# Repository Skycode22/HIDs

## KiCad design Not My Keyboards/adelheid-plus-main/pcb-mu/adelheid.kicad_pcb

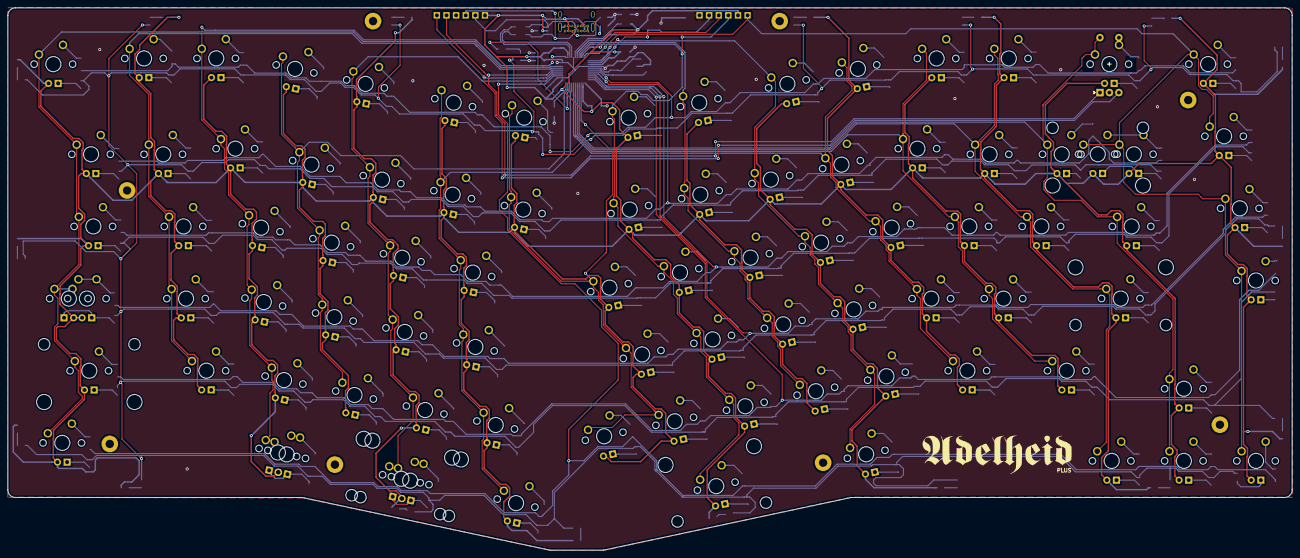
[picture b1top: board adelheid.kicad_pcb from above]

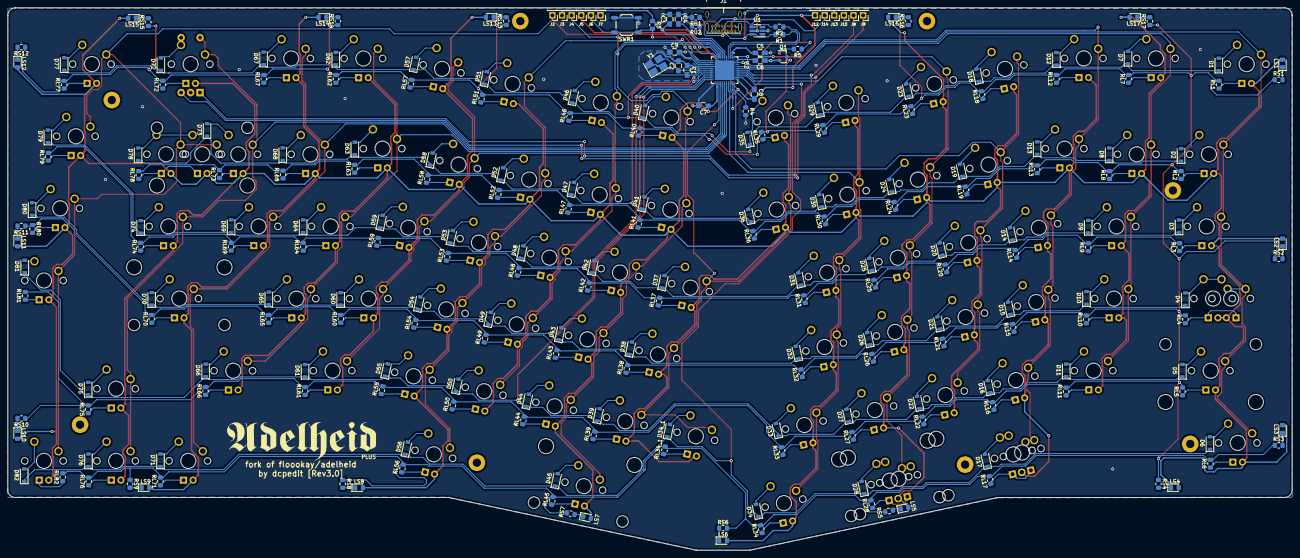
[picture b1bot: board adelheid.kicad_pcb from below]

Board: 2 copper layers, 339.1 x 143.2 mm, 332 parts (235 on the bottom side), 223 nets.

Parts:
 G2: LOGO; adelheid-logo
C1, C2: 22pF; C_0805_HandSoldering
C3: 10uF; C_0805_HandSoldering
C4: 1uF (±10%); C_0805_HandSoldering
C5: 1uF; C_0805_HandSoldering
C6, C7, C8, C9: 0.1uF; C_0805_HandSoldering
D1, D2, D3, D4, D5, D6, D7, D8, D9, D10, D11, D12, D13, D14, D15, D16, D17, D18, D19, D20, D21, D22, D23, D24, D25, D26, D27, D28, D29, D30, D31, D32, D33, D34, D34_1, D35, D36, D37, D38, D39, D40, D41, D42, D43, D44, D45, D46, D47, D48, D49, D50, D51, D52, D53, D54, D55, D56, D57, D58, D59, D60, D61, D62, D63, D64, D65, D66, D67, D68, D69, D70, D71, D72, D73, D74, D75, D76, D77, D78, D79, D80, D81, D82: D; D_SOD-123
G1: LOGO; adelheid-logo
H1, H2, H3, H4, H5, H6, H7, H8: MountingHole; MountingHole_2.2mm_M2_Pad
J1: USB_C_Receptacle_USB2.0; USB_C_GCT_USB4085
J2: MISO; Pin_Header_Straight_1x01_Pitch2.54mm
J3, J12: VCC; Pin_Header_Straight_1x01_Pitch2.54mm
J4: SCK; Pin_Header_Straight_1x01_Pitch2.54mm
J5: MOSI; Pin_Header_Straight_1x01_Pitch2.54mm
J6: RES; Pin_Header_Straight_1x01_Pitch2.54mm
J7, J15: GND; Pin_Header_Straight_1x01_Pitch2.54mm
J8: PF4; Pin_Header_Straight_1x01_Pitch2.54mm
J9: PF5; Pin_Header_Straight_1x01_Pitch2.54mm
J13: D+; Pin_Header_Straight_1x01_Pitch2.54mm
J14: D-; Pin_Header_Straight_1x01_Pitch2.54mm
LS1, LS2, LS3, LS4, LS5, LS6, LS7, LS8, LS9, LS10, LS11, LS12, LS13, LS14, LS15, LS16, LS17: LED; LED_0805_2012Metric_Pad1.15x1.40mm_HandSolder
MX1, MX2, MX7, MX8, MX9, MX10, MX11, MX12, MX13, MX14, MX15, MX16, MX18, MX19, MX20, MX21, MX22, MX23, MX24, MX25, MX26, MX27, MX29, MX30, MX31, MX32, MX33, MX34, MX34_1, MX35, MX36, MX37, MX38, MX39, MX40, MX41, MX42, MX43, MX44, MX46, MX47, MX48, MX49, MX50, MX51, MX52, MX53, MX54, MX55, MX57, MX58, MX59, MX60, MX61, MX62, MX63, MX64, MX65, MX67, MX68, MX69, MX71, MX72, MX73, MX75, MX76, MX77, MX78, MX79, MX80, MX81, MX82: MX-LED; MXOnly-1U
MX3, MX6, MX17, MX56, MX74: MX-LED; MXOnly-1.5U
MX4, MX66: MX-LED; MXOnly-1.75U
MX4_1: MX-LED; MXOnly-1.75U-FLIPPED
MX5: MX-LED; MXOnly-2.25U
MX17.125: MX-LED; MXOnly-1.25U
MX28: MX-LED; MXOnly-2U-ReversedStabilizers
MX28.225, MX70: MX-LED; MXOnly-2.25U-ReversedStabilizers
MX45: MX-LED; MXOnly-2.75U-ReversedStabilizers
MX78_1: MX-LED; MXOnly-2U
Q1: 2N7002; SOT-23
R1, R2: 22; R_0805_2012Metric_Pad1.15x1.40mm_HandSolder
R3, R4: 10K; R_0805_2012Metric_Pad1.15x1.40mm_HandSolder
R5: 1.5K; R_0805_2012Metric_Pad1.15x1.40mm_HandSolder
RE_SW1: Rotary_Encoder_Switch; RotaryEncoder_EC11
RL1, RL2, RL3, RL4, RL5, RL6, RL7, RL8, RL9, RL10, RL11, RL12, RL13, RL14, RL15, RL16, RL17, RL18, RL19, RL20, RL21, RL22, RL23, RL24, RL25, RL26, RL27, RL28, RL29, RL30, RL31, RL32, RL33, RL34, RL35, RL36, RL37, RL38, RL39, RL40, RL41, RL42, RL43, RL44, RL45, RL46, RL47, RL48, RL49, RL50, RL51, RL52, RL53, RL54, RL55, RL56, RL57, RL58, RL59, RL60, RL61, RL62, RL63, RL64, RL65, RL66, RL67, RL68, RL69, RL70, RL71, RL72, RL73, RL74, RL75, RL76, RL77, RL78, RL79, RL80, RL81, RL82: R; R_0805_2012Metric_Pad1.15x1.40mm_HandSolder
RL34_1: R; R_0805_2012Metric_Pad1.20x1.40mm_HandSolder
RS1, RS2, RS3, RS4, RS5, RS6, RS7, RS8, RS9, RS10, RS11, RS12, RS13, RS14, RS15, RS16, RS17: R; R_0805_2012Metric_Pad1.15x1.40mm_HandSolder
RU1, RU2: 5.1K; R_0805_2012Metric_Pad1.20x1.40mm_HandSolder
SWR1: SW_Push; SW_SPST_TL3342
U1: USBLC6-2SC6; SOT-23-6_Handsoldering
U2: ATmega32U4-MU; QFN50P700X700X100-45N
Y1: Crystal_GND24; Crystal_SMD_SeikoEpson_FA238-4pin_3.2x2.5mm_HandSoldering

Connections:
/MISO: J2.1, MX77.1, MX78.1, MX78_1.1, MX79.1, MX80.1, MX81.1, MX82.1, U2.11
/MOSI: J5.1, U2.10
/PF4: J8.1, RE_SW1.A, U2.39
/PF5: J9.1, RE_SW1.B, U2.38
/SCK: J4.1, MX40.1, MX41.1, MX42.1, MX43.1, MX44.1, MX45.1, U2.9
/col0: MX1.1, MX2.1, MX3.1, MX4.1, MX4_1.1, MX5.1, MX6.1, U2.41
/col1: MX7.1, MX8.1, MX9.1, MX10.1, MX11.1, U2.40
/col2: MX12.1, MX13.1, MX14.1, MX15.1, MX16.1, MX17.1, MX17.125.1, U2.1
/col3: MX18.1, MX19.1, MX20.1, MX21.1, MX22.1, U2.32
/col4: MX23.1, MX24.1, MX25.1, MX26.1, MX27.1, MX28.1, MX28.225.1, U2.37
/col5: MX29.1, MX30.1, MX31.1, MX32.1, MX33.1, MX34.1, U2.30
/col6: MX34_1.1, MX35.1, MX36.1, MX37.1, MX38.1, MX39.1, U2.25
/col8: MX46.1, MX47.1, MX48.1, MX49.1, MX50.1, U2.8
/col9: MX51.1, MX52.1, MX53.1, MX54.1, MX55.1, MX56.1, U2.12
/col10: MX57.1, MX58.1, MX59.1, MX60.1, MX61.1, U2.29
/col11: MX62.1, MX63.1, MX64.1, MX65.1, MX66.1, U2.28
/col12: MX67.1, MX68.1, MX69.1, MX70.1, MX71.1, U2.27
/col13: MX72.1, MX73.1, MX74.1, MX75.1, MX76.1, RE_SW1.S2, U2.26
/ledGND: Q1.3, RL1.2, RL2.2, RL3.2, RL4.2, RL5.2, RL6.2, RL7.2, RL8.2, RL9.2, RL10.2, RL11.2, RL12.2, RL13.2, RL14.2, RL15.2, RL16.2, RL17.2, RL18.2, RL19.2, RL20.2, RL21.2, RL22.2, RL23.2, RL24.2, RL25.2, RL26.2, RL27.2, RL28.2, RL29.2, RL30.2, RL31.2, RL32.2, RL33.2, RL34.2, RL34_1.2, RL35.2, RL36.2, RL37.2, RL38.2, RL39.2, RL40.2, RL41.2, RL42.2, RL43.2, RL44.2, RL45.2, RL46.2, RL47.2, RL48.2, RL49.2, RL50.2, RL51.2, RL52.2, RL53.2, RL54.2, RL55.2, RL56.2, RL57.2, RL58.2, RL59.2, RL60.2, RL61.2, RL62.2, RL63.2, RL64.2, RL65.2, RL66.2, RL67.2, RL68.2, RL69.2, RL70.2, RL71.2, RL72.2, RL73.2, RL74.2, RL75.2, RL76.2, RL77.2, RL78.2, RL79.2, RL80.2, RL81.2, RL82.2, RS1.1, RS2.1, RS3.1, RS4.1, RS5.1, RS6.1, RS7.1, RS8.1, RS9.1, RS10.1, RS11.1, RS12.1, RS13.1, RS14.1, RS15.1, RS16.1, RS17.1
/row0: D1.1, D7.1, D12.1, D18.1, D23.1, D29.1, D35.1, D40.1, D46.1, D51.1, D57.1, D62.1, D67.1, D72.1, D77.1, U2.18
/row1: D2.1, D8.1, D13.1, D19.1, D24.1, D30.1, D36.1, D41.1, D47.1, D52.1, D58.1, D63.1, D68.1, D73.1, D78.1, U2.19
/row2: D3.1, D9.1, D14.1, D20.1, D25.1, D31.1, D37.1, D42.1, D48.1, D53.1, D59.1, D64.1, D69.1, D74.1, D79.1, U2.20
/row3: D4.1, D10.1, D15.1, D21.1, D26.1, D32.1, D38.1, D43.1, D49.1, D54.1, D60.1, D65.1, D70.1, D80.1, U2.21
/row4: D5.1, D11.1, D16.1, D22.1, D27.1, D33.1, D39.1, D44.1, D50.1, D55.1, D61.1, D66.1, D75.1, D81.1, U2.22
/row5: D6.1, D17.1, D28.1, D34.1, D34_1.1, D45.1, D56.1, D71.1, D76.1, D82.1, U2.36
/~RES~: J6.1, R3.2, SWR1.2, U2.13
D+: R1.1, U2.4
D-: R2.1, U2.3
GND: C1.1, C2.2, C3.2, C4.2, C5.2, C6.2, C7.2, C8.2, C9.2, J1.A1, J1.A12, J1.B1, J1.B12, J1.S1, J7.1, J15.1, Q1.2, R4.2, RE_SW1.C, RU1.2, RU2.2, SWR1.1, U1.2, U2.5, U2.15, U2.23, U2.35, U2.43, U2.45, Y1.2, Y1.4
unnamed: C4.1, U2.6
unnamed: D1.2, MX1.2
unnamed: D2.2, MX2.2
unnamed: D3.2, MX3.2
unnamed: D4.2, MX4.2, MX4_1.2
unnamed: D5.2, MX5.2
unnamed: D6.2, MX6.2
unnamed: D7.2, MX7.2
unnamed: D8.2, MX8.2
unnamed: D9.2, MX9.2
unnamed: D10.2, MX10.2
unnamed: D11.2, MX11.2
unnamed: D12.2, MX12.2
unnamed: D13.2, MX13.2
unnamed: D14.2, MX14.2
unnamed: D15.2, MX15.2
unnamed: D16.2, MX16.2
unnamed: D17.2, MX17.2, MX17.125.2
unnamed: D18.2, MX18.2
unnamed: D19.2, MX19.2
unnamed: D20.2, MX20.2
unnamed: D21.2, MX21.2
unnamed: D22.2, MX22.2
unnamed: D23.2, MX23.2
unnamed: D24.2, MX24.2
unnamed: D25.2, MX25.2
unnamed: D26.2, MX26.2
unnamed: D27.2, MX27.2
unnamed: D28.2, MX28.2, MX28.225.2
unnamed: D29.2, MX29.2
unnamed: D30.2, MX30.2
unnamed: D31.2, MX31.2
unnamed: D32.2, MX32.2
unnamed: D33.2, MX33.2
unnamed: D34.2, MX34.2
unnamed: D34_1.2, MX34_1.2
unnamed: D35.2, MX35.2
unnamed: D36.2, MX36.2
unnamed: D37.2, MX37.2
unnamed: D38.2, MX38.2
unnamed: D39.2, MX39.2
unnamed: D40.2, MX40.2
unnamed: D41.2, MX41.2
unnamed: D42.2, MX42.2
unnamed: D43.2, MX43.2
unnamed: D44.2, MX44.2
unnamed: D45.2, MX45.2
unnamed: D46.2, MX46.2
unnamed: D47.2, MX47.2
unnamed: D48.2, MX48.2
unnamed: D49.2, MX49.2
unnamed: D50.2, MX50.2
unnamed: D51.2, MX51.2
unnamed: D52.2, MX52.2
unnamed: D53.2, MX53.2
unnamed: D54.2, MX54.2
unnamed: D55.2, MX55.2
unnamed: D56.2, MX56.2
unnamed: D57.2, MX57.2
unnamed: D58.2, MX58.2
unnamed: D59.2, MX59.2
unnamed: D60.2, MX60.2
unnamed: D61.2, MX61.2
unnamed: D62.2, MX62.2
unnamed: D63.2, MX63.2
unnamed: D64.2, MX64.2
unnamed: D65.2, MX65.2
unnamed: D66.2, MX66.2
unnamed: D67.2, MX67.2
unnamed: D68.2, MX68.2
unnamed: D69.2, MX69.2
unnamed: D70.2, MX70.2
unnamed: D71.2, MX71.2
unnamed: D72.2, MX72.2, RE_SW1.S1
unnamed: D73.2, MX73.2
unnamed: D74.2, MX74.2
unnamed: D75.2, MX75.2
unnamed: D76.2, MX76.2
unnamed: D77.2, MX77.2
unnamed: D78.2, MX78.2, MX78_1.2
unnamed: D79.2, MX79.2
unnamed: D80.2, MX80.2
unnamed: D81.2, MX81.2
unnamed: D82.2, MX82.2
unnamed: J1.A5, RU1.1
unnamed: J1.A6, J1.B6, J13.1, R1.2, U1.6
unnamed: J1.A7, J1.B7, J14.1, R2.2, U1.4
unnamed: J1.B5, RU2.1
unnamed: LS1.1, RS1.2
unnamed: LS2.1, RS2.2
unnamed: LS3.1, RS3.2
unnamed: LS4.1, RS4.2
unnamed: LS5.1, RS5.2
unnamed: LS6.1, RS6.2
unnamed: LS7.1, RS7.2
unnamed: LS8.1, RS8.2
unnamed: LS9.1, RS9.2
unnamed: LS10.1, RS10.2
unnamed: LS11.1, RS11.2
unnamed: LS12.1, RS12.2
unnamed: LS13.1, RS13.2
unnamed: LS14.1, RS14.2
unnamed: LS15.1, RS15.2
unnamed: LS16.1, RS16.2
unnamed: LS17.1, RS17.2
unnamed: MX1.4, RL1.1
unnamed: MX2.4, RL2.1
unnamed: MX3.4, RL3.1
unnamed: MX4.4, MX4_1.4, RL4.1
unnamed: MX5.4, RL5.1
unnamed: MX6.4, RL6.1
unnamed: MX7.4, RL7.1
unnamed: MX8.4, RL8.1
unnamed: MX9.4, RL9.1
unnamed: MX10.4, RL10.1
unnamed: MX11.4, RL11.1
unnamed: MX12.4, RL12.1
unnamed: MX13.4, RL13.1
unnamed: MX14.4, RL14.1
unnamed: MX15.4, RL15.1
unnamed: MX16.4, RL16.1
unnamed: MX17.4, MX17.125.4, RL17.1
unnamed: MX18.4, RL18.1
unnamed: MX19.4, RL19.1
unnamed: MX20.4, RL20.1
unnamed: MX21.4, RL21.1
unnamed: MX22.4, RL22.1
unnamed: MX23.4, RL23.1
unnamed: MX24.4, RL24.1
unnamed: MX25.4, RL25.1
unnamed: MX26.4, RL26.1
unnamed: MX27.4, RL27.1
unnamed: MX28.4, MX28.225.4, RL28.1
unnamed: MX29.4, RL29.1
unnamed: MX30.4, RL30.1
unnamed: MX31.4, RL31.1
unnamed: MX32.4, RL32.1
unnamed: MX33.4, RL33.1
unnamed: MX34.4, RL34.1
unnamed: MX34_1.4, RL34_1.1
unnamed: MX35.4, RL35.1
unnamed: MX36.4, RL36.1
unnamed: MX37.4, RL37.1
unnamed: MX38.4, RL38.1
unnamed: MX39.4, RL39.1
unnamed: MX40.4, RL40.1
unnamed: MX41.4, RL41.1
unnamed: MX42.4, RL42.1
unnamed: MX43.4, RL43.1
unnamed: MX44.4, RL44.1
unnamed: MX45.4, RL45.1
unnamed: MX46.4, RL46.1
unnamed: MX47.4, RL47.1
unnamed: MX48.4, RL48.1
unnamed: MX49.4, RL49.1
unnamed: MX50.4, RL50.1
unnamed: MX51.4, RL51.1
unnamed: MX52.4, RL52.1
unnamed: MX53.4, RL53.1
unnamed: MX54.4, RL54.1
unnamed: MX55.4, RL55.1
unnamed: MX56.4, RL56.1
unnamed: MX57.4, RL57.1
unnamed: MX58.4, RL58.1
unnamed: MX59.4, RL59.1
unnamed: MX60.4, RL60.1
unnamed: MX61.4, RL61.1
unnamed: MX62.4, RL62.1
unnamed: MX63.4, RL63.1
unnamed: MX64.4, RL64.1
unnamed: MX65.4, RL65.1
unnamed: MX66.4, RL66.1
unnamed: MX67.4, RL67.1
unnamed: MX68.4, RL68.1
unnamed: MX69.4, RL69.1
unnamed: MX70.4, RL70.1
unnamed: MX71.4, RL71.1
unnamed: MX72.4, RL72.1
unnamed: MX73.4, RL73.1
unnamed: MX74.4, RL74.1
unnamed: MX75.4, RL75.1
unnamed: MX76.4, RL76.1
unnamed: MX77.4, RL77.1
unnamed: MX78.4, MX78_1.4, RL78.1
unnamed: MX79.4, RL79.1
unnamed: MX80.4, RL80.1
unnamed: MX81.4, RL81.1
unnamed: MX82.4, RL82.1
unnamed: Q1.1, R5.2
unnamed: R4.1, U2.33
unnamed: R5.1, U2.31
VCC: C3.1, C5.1, C6.1, C7.1, C8.1, C9.1, J1.A4, J1.A9, J1.B4, J1.B9, J3.1, J12.1, LS1.2, LS2.2, LS3.2, LS4.2, LS5.2, LS6.2, LS7.2, LS8.2, LS9.2, LS10.2, LS11.2, LS12.2, LS13.2, LS14.2, LS15.2, LS16.2, LS17.2, MX1.3, MX2.3, MX3.3, MX4.3, MX4_1.3, MX5.3, MX6.3, MX7.3, MX8.3, MX9.3, MX10.3, MX11.3, MX12.3, MX13.3, MX14.3, MX15.3, MX16.3, MX17.3, MX17.125.3, MX18.3, MX19.3, MX20.3, MX21.3, MX22.3, MX23.3, MX24.3, MX25.3, MX26.3, MX27.3, MX28.3, MX28.225.3, MX29.3, MX30.3, MX31.3, MX32.3, MX33.3, MX34.3, MX34_1.3, MX35.3, MX36.3, MX37.3, MX38.3, MX39.3, MX40.3, MX41.3, MX42.3, MX43.3, MX44.3, MX45.3, MX46.3, MX47.3, MX48.3, MX49.3, MX50.3, MX51.3, MX52.3, MX53.3, MX54.3, MX55.3, MX56.3, MX57.3, MX58.3, MX59.3, MX60.3, MX61.3, MX62.3, MX63.3, MX64.3, MX65.3, MX66.3, MX67.3, MX68.3, MX69.3, MX70.3, MX71.3, MX72.3, MX73.3, MX74.3, MX75.3, MX76.3, MX77.3, MX78.3, MX78_1.3, MX79.3, MX80.3, MX81.3, MX82.3, R3.1, U1.5, U2.2, U2.7, U2.14, U2.24, U2.34, U2.44
XTAL1: C1.2, U2.17, Y1.1
XTAL2: C2.1, U2.16, Y1.3
